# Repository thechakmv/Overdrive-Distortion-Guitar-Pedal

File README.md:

# Dual-Stage Overdrive & Distortion Guitar Pedal

I created analog guitar effects pedal with two independent, switchable gain stages featuring deliberately opposite midrange voicings to achieve classic Thrash metal rhythm and lead tones: a soft-clipping overdrive with a **mid-boost** (+6 dB at 800 Hz) and a hard-clipping distortion with a **mid-scoop** (−6 to −10 dB across 400–800 Hz). The Pedal features a single-knob passive tone control, and volume control as well. Each stage has true-bypass switching, so the two can run independently or be cascaded for stacked high-gain tones.

## Highlights

- Designed and simulated in LTSpice; verified Bode plots, transient behavior, and FFT spectrum on hardware
- Two-stage analog signal chain built around TL072 JFET-input op-amps
- True-bypass per stage via 3PDT footswitches; both stages engage simultaneously for cascaded gain
- Passive Twin-T notch filter for the distortion mid-scoop voicing
- Single 9 V DC supply, ~30 mA total current draw
- PCB layout in KiCad with attention to signal integrity, star-ground topology, and inter-stage isolation

## Signal Flow

```
                                                         
 Guitar ─> Input ─┬─> OD Stage ──┬─> Distortion ──┬─> Tone ─> Volume ─> Output ─> Amp
          Buffer  │   (soft clip,│   (hard clip + │  (LPF)    (audio)   Buffer
          (TL072) │   mid-boost) │   Twin-T scoop)│
                  │              │                │
                  ▼              ▼                ▼
                SW1 3PDT        SW2 3PDT       Always
                true bypass     true bypass    in signal path
```

When both footswitches are engaged, the OD output feeds the distortion stage input, producing cascaded high-gain saturation. Each stage can also run alone for cleaner crunch or for chunkier rhythm tones.

## Design Specifications

| Parameter | Value |
|---|---|
| Supply | 9 V DC, center-negative, ~30 mA |
| Frequency response (clean path) | Flat ±0.5 dB across 20 Hz – 20 kHz |
| OD voicing | +6 dB peak at 800 Hz; corners at 720 Hz and ~6 kHz |
| OD gain range | 0 dB to +41 dB |
| OD clipping | Soft, symmetric, ±0.6 V (1N4148 anti-parallel in feedback) |
| Distortion voicing | −6 to −10 dB notch centered at ~700 Hz |
| Distortion gain range | +14 dB to +54 dB |
| Distortion clipping | Hard, symmetric, ±0.6 V (1N4148 to Vref) |

## Design Philosophy

Where most pedals use a single clipping topology, this design uses two intentionally distinct stages whose characters complement each other when cascaded.

The **overdrive stage** is a Tube Screamer-derived non-inverting topology with silicon diodes inside the feedback loop. The feedback RC network forms a band-pass response: lows roll off below 720 Hz and highs roll off above ~6 kHz at maximum gain. Inside the band the gradual diode conduction produces soft clipping that preserves the dry signal underneath the saturation, giving the characteristic transparent overdrive sound.

The **distortion stage** uses an inverting topology with diodes clamping the op-amp output directly to the Vref node. This produces hard, square-wave clipping rich in odd harmonics. The clipped signal then feeds a passive Twin-T notch filter centered near 700 Hz, carving out the boxy midrange while leaving low and high content intact — the classic scooped-mid metal voicing.

The two stages are independently switchable: OD alone for crunch, distortion alone for chunky rhythm work, or both stacked for full-saturation lead tones.

## Repository Structure

```
├── ltspice/
│   ├── od_stage.asc
│   ├── distortion_stage.asc
│   └── Overdrive_Distortion_Schematic.asc              
├── kicad/
│   ├── pedal.kicad_pro             Project file
│   ├── pedal.kicad_sch             Schematic
│   ├── pedal.kicad_pcb             Board layout
│   └── gerbers/                    Fabrication output (zipped Gerbers + drill)
└── images/
    ├── frequency_response.png      Measured Bode plots
    ├── pcb_schematic.png          Spectrum analyzer captures
    └── pcb_3d.png                  Oscilloscope captures
```

## Tools

**Software:** LTSpice, KiCad 7

**Test equipment:** oscilloscope (FFT capable), signal generator, multimeter, soldering iron

## Build Process

1. **Simulate.** Run AC and transient analyses in LTSpice for each stage. Verify gain curves, clipping shape, and Vref stability under load. Use `.step` to sweep gain pot values and see the response variation across the control range.

2. **Breadboard.** Build stage-by-stage with bench power. Validate against simulation results with scope and FFT. This is the stage to tune by ear — swap diodes (Si vs. LED vs. asymmetric), tweak the scoop center frequency, dial in the gain ranges.

3. **PCB.** Re-capture the validated schematic in KiCad, assign through-hole footprints, lay out the board with the panel-component headers anchored to enclosure positions. Generate Gerbers and fabricate via JLCPCB or OSH Park.

**In Progress:**
1. **Assemble.** Populate the PCB; wire off-board panel components (pots, footswitches, jacks); mount in enclosure.

2. **Verify.** Measure assembled pedal's frequency response and FFT; compare against simulation predictions.

## Testing & Verification

The hardware was validated against simulation using:

**Bode plots:** swept sine across 20 Hz – 20 kHz, output captured on oscilloscope, magnitude plotted in dB. Measured curve matches LTSpice AC analysis within ±2 dB across the band.

**FFT analysis:** 1 kHz sine input at each stage's clipping threshold, output FFT'd to verify harmonic content. The OD stage shows soft-clip characteristic harmonic roll-off; the distortion stage shows hard-clip odd-harmonic series with a clear notch at ~700 Hz after the Twin-T.

## Design Issues Encountered (and Fixed)

Three non-obvious problems came up during simulation and breadboarding that are worth documenting:

**Vref instability under heavy distortion.** The hard-clipping diodes were pumping asymmetric current pulses into the unbuffered Vref node, dragging it from 4.5 V down toward 1 V during sustained clipping. Fixed by adding a 1 kΩ series resistor between the distortion op-amp's output and the diode pair, limiting peak diode current and preserving Vref bias integrity.

**High-frequency oscillation at high gain.** The TL072 stages were prone to oscillation when driving capacitive loads (cable runs, coupling caps). Fixed by adding a 470 Ω series isolation resistor between each op-amp output and its capacitive load, with feedback taken before the resistor.

**Switch-engage pop.** Resolved by adding 1 MΩ pull-down resistors on both sides of every coupling cap that interfaces with a footswitch, ensuring no DC charge accumulates on the disconnected side of the cap during bypass.

## Skills Demonstrated

- Analog circuit design with op-amps (inverting, non-inverting, follower topologies)
- Frequency-response shaping via reactive feedback networks
- Soft-clipping vs. hard-clipping topology selection and harmonic analysis
- Single-supply audio biasing: Vref generation, AC coupling, bypass strategy
- Passive filter design (Twin-T notch with derivation of component ratios)
- SPICE simulation: AC sweep, transient analysis, FFT, parametric stepping
- PCB layout for analog audio: ground topology, decoupling, inter-stage isolation
- Hardware validation against simulation with scope and spectrum analyzer

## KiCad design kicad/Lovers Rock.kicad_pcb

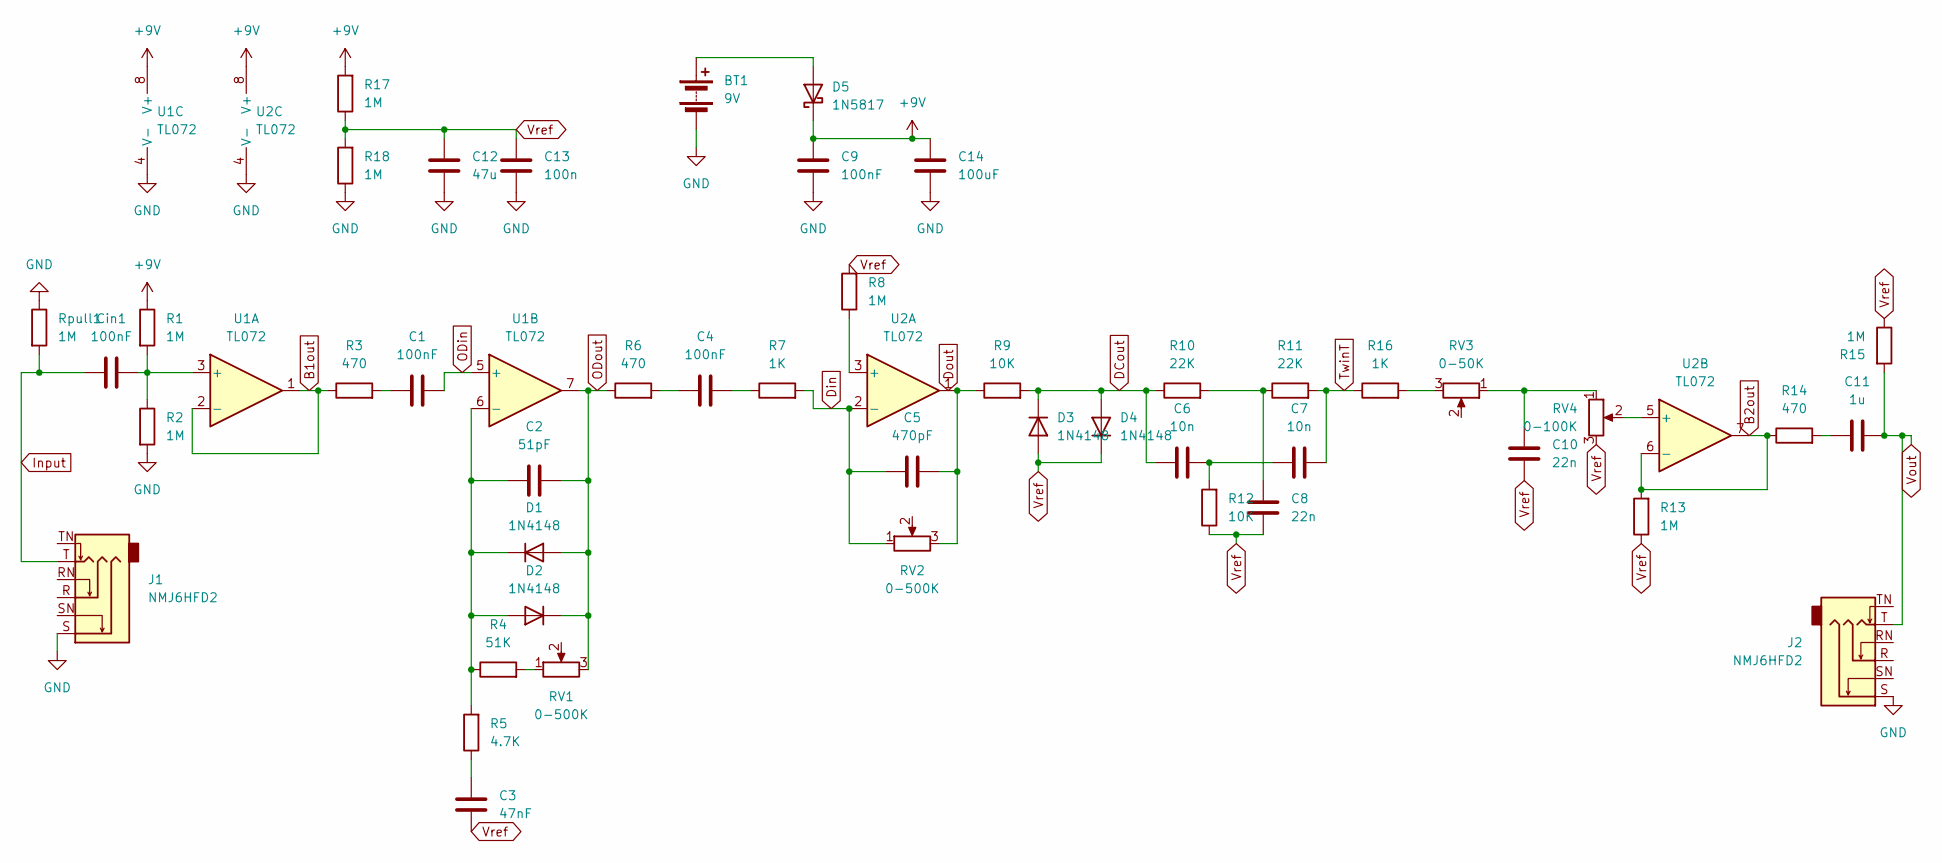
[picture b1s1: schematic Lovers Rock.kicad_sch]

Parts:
BT1: 9V; BarrelJack_CLIFF_FC681465S_SMT_Horizontal
C1, C4: 100nF; C_Disc_D5.0mm_W2.5mm_P2.50mm
C2: 51pF; C_Disc_D3.8mm_W2.6mm_P2.50mm
C3: 47nF; C_Disc_D3.8mm_W2.6mm_P2.50mm
C5: 470pF; C_Disc_D4.7mm_W2.5mm_P5.00mm
C6, C7: 10n; C_Disc_D4.7mm_W2.5mm_P5.00mm
C8, C10: 22n; C_Disc_D4.7mm_W2.5mm_P5.00mm
C9: 100nF; CP_Radial_D7.5mm_P2.50mm
C11: 1u; CP_Radial_D6.3mm_P2.50mm
C12: 47u; CP_Radial_D7.5mm_P2.50mm
C13: 100n; C_Disc_D5.0mm_W2.5mm_P2.50mm
C14: 100uF; CP_Radial_D7.5mm_P2.50mm
Cin1: 100nF; C_Disc_D5.0mm_W2.5mm_P2.50mm
D1, D2, D3, D4: 1N4148; D_DO-35_SOD27_P7.62mm_Horizontal
D5: 1N5817; D_DO-41_SOD81_P10.16mm_Horizontal
J1, J2: NMJ6HFD2; Jack_6.35mm_Neutrik_NMJ6HFD2_Horizontal
R1, R2, R8, R13, R15, R17, R18: 1M; R_Axial_DIN0207_L6.3mm_D2.5mm_P7.62mm_Horizontal
R3, R6, R14: 470; R_Axial_DIN0207_L6.3mm_D2.5mm_P7.62mm_Horizontal
R4: 51K; R_Axial_DIN0207_L6.3mm_D2.5mm_P7.62mm_Horizontal
R5: 4.7K; R_Axial_DIN0207_L6.3mm_D2.5mm_P7.62mm_Horizontal
R7, R16: 1K; R_Axial_DIN0207_L6.3mm_D2.5mm_P7.62mm_Horizontal
R9, R12: 10K; R_Axial_DIN0207_L6.3mm_D2.5mm_P7.62mm_Horizontal
R10, R11: 22K; R_Axial_DIN0207_L6.3mm_D2.5mm_P7.62mm_Horizontal
RV1, RV2: 0-500K; Potentiometer_Bourns_PTV09A-1_Single_Vertical
RV3: 0-50K; Potentiometer_Bourns_PTV09A-1_Single_Vertical
RV4: 0-100K; Potentiometer_Bourns_PTV09A-1_Single_Vertical
Rpull1: 1M; R_Axial_DIN0207_L6.3mm_D2.5mm_P7.62mm_Horizontal
U1, U2: TL072; DIP-8_W7.62mm_Socket

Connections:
+9V: C9.2, C14.2, D5.1 (K), R1.1, R17.2, U1.8 (V+), U2.8 (V+)
B1out: R3.1, U1.1, U1.2 (-)
B2out: R13.2, R14.1, U2.6 (-), U2.7
DCout: C6.1, D3.1 (K), D4.2 (A), R9.2, R10.1
Din: C5.1, R7.2, RV2.1, U2.2 (-)
GND: BT1.2 (-), C9.1, C12.1, C13.1, C14.1, J1.S, J2.S, R2.2, R18.1, Rpull1.1, U1.4 (V-), U2.4 (V-)
Input: Cin1.1, J1.T, Rpull1.2
unnamed: BT1.1 (+), D5.2 (A)
unnamed: C1.1, R3.2
unnamed: C3.2, R5.1
unnamed: C4.1, R6.2
unnamed: C4.2, R7.1
unnamed: C5.2, R9.1, RV2.3, U2.1
unnamed: C6.2, C7.1, R12.2
unnamed: C8.2, R10.2, R11.1
unnamed: C10.2, RV3.1, RV4.1
unnamed: C11.2, R14.2
unnamed: C2.1, D1.1 (K), D2.2 (A), R4.1, R5.2, U1.6 (-)
unnamed: R4.2, RV1.1
unnamed: R16.2, RV3.3
unnamed: Cin1.2, R1.2, R2.1, U1.3 (+)
unnamed: R8.1, U2.3 (+)
unnamed: RV4.2, U2.5 (+)
ODin: C1.2, U1.5 (+)
ODout: C2.2, D1.2 (A), D2.1 (K), R6.1, RV1.3, U1.7
TwinT: C7.2, R11.2, R16.1
Vout: C11.1, J2.T, R15.2
Vref: C3.1, C8.1, C10.1, C12.2, C13.2, D3.2 (A), D4.1 (K), R8.2, R12.1, R13.1, R15.1, R17.1, R18.2, RV4.3

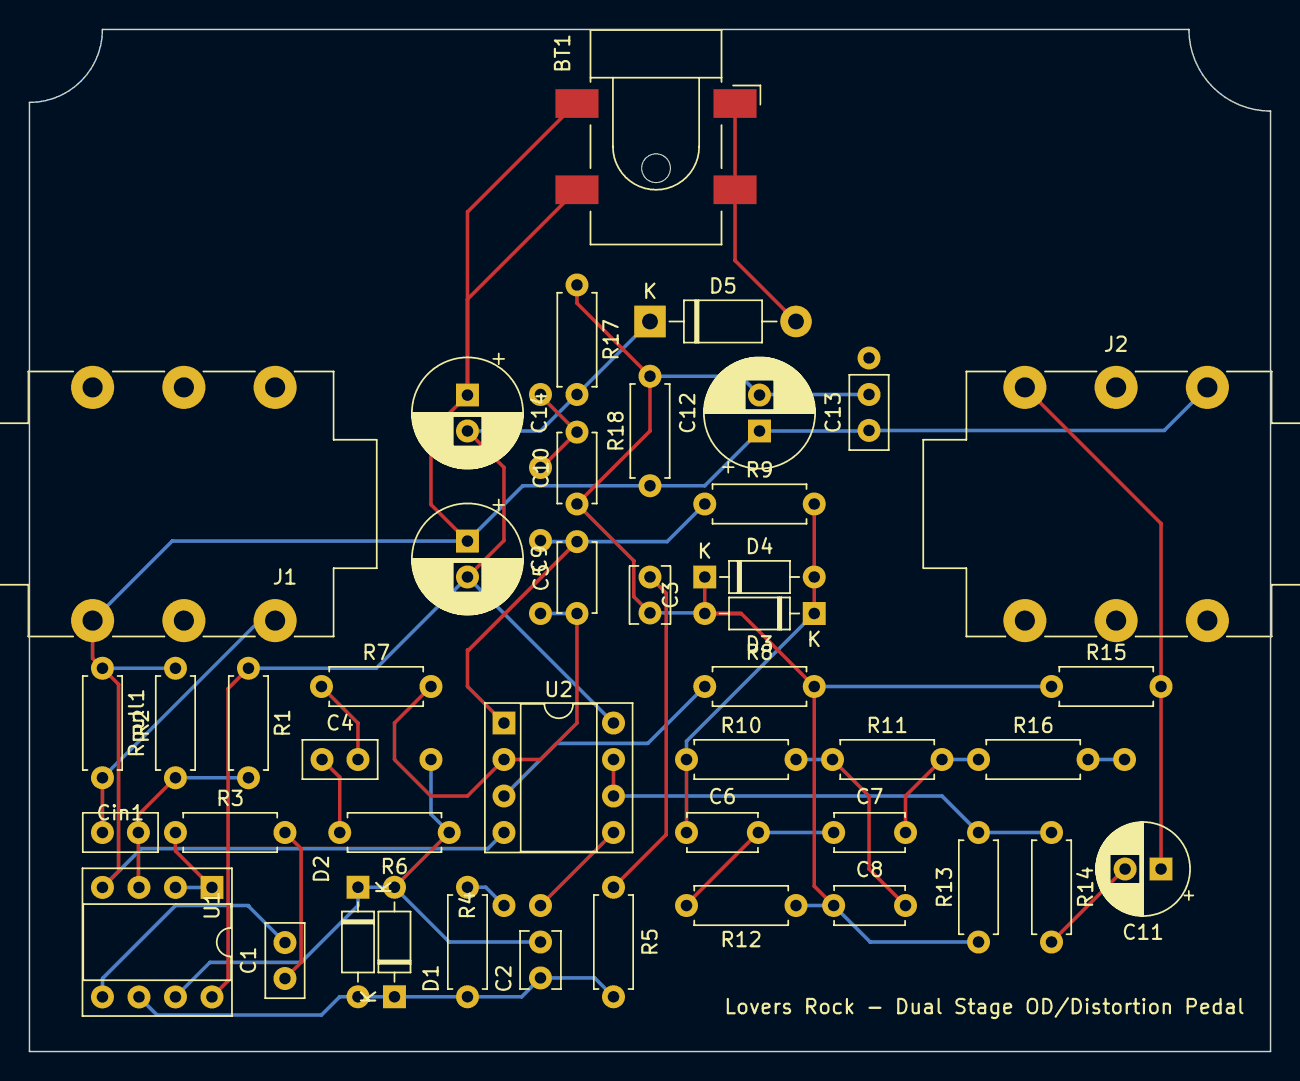
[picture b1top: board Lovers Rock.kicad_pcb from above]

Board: 2 copper layers, 86.4 x 71.1 mm, 44 parts (0 on the bottom side), 24 nets.

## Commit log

2026-05-17 Uploaded Files
2026-05-18 Updated Readme, and file structure
